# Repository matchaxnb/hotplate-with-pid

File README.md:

# One way of doing it

Do as I have: modify a hot plate and add a SSR within it to turn it on and off on demand.

# Another smarter way

Have your SSR enabling/disabling a regular plug or power cord and plug your hotplate with full-on settings in said plug.

# Observations

Put the thermocouple sensor on the outside of your plate, under aluminium foil. Inside a hot plate enclosure things remain hot
for long.

This code is ugly but at least it does not abuse delay().

first arduino project.

# Notes

WIP

not ready.

need to make it work better.

especially, currently it's staying in any given state for just the time it says in the steps. I need to slice time better.

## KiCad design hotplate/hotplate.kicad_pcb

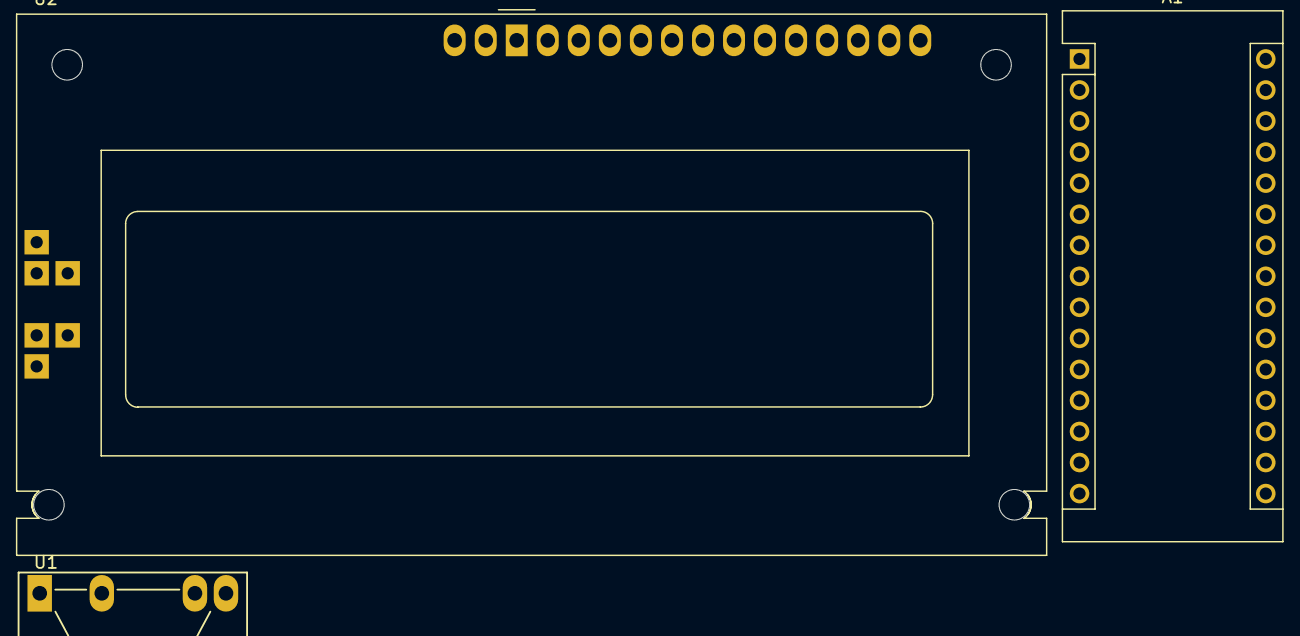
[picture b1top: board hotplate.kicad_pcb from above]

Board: 2 copper layers, 3 parts (0 on the bottom side), 8 nets, no tracks yet.

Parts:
A1: Arduino_Nano_Every; Arduino_Nano
U1: S102S01; SIP4_Sharp-SSR_P7.62mm_Straight
U2: RC1602A

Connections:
/A_D6: A1.9 (D6), U2.4 (RS)
/A_D7: A1.10 (D7), U2.5 (R/W)
/A_D8: A1.11 (D8), U2.6 (E)
/A_D9: A1.12 (D9), U2.11 (DB4)
/A_D10: A1.13 (D10), U2.12 (DB5)
/A_D11: A1.14 (MOSI), U2.13 (DB6)
/A_D12: A1.15 (MISO), U2.14 (DB7)
/GND: A1.4 (GND), A1.29 (GND), U1.4

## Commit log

2022-08-25 feat(reflow): add basic code and observations
2022-08-25 docs(kicad): add kicad schematics (starteR)
2022-08-25 docs(rant): add some observations
